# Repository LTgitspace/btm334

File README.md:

# BTM334 Audio Receiver (Archived)

## Project Status: Deprecated & Unmaintained

This repository is **no longer actively maintained or developed**. 

The hardware and firmware designs preserved here represent legacy prototype iterations based on the **Qualcomm QCC3034 (BTM334)** module and external I2S DACs (ES9023P / PCM5102A). This repository is retained strictly for historical and architectural reference.

---

## Technical Migration: ESP32 + LDAC + Custom App

Active development has fully pivoted to an **Espressif ESP32-based architecture** delivering high-resolution wireless audio paired with a dedicated control software ecosystem.

### Key Architectural Shifts

1. **Audio Codec: Sony LDAC Integration**
   * Migrated from Qualcomm proprietary codecs (aptX / aptX HD / aptX LL) to **Sony LDAC**.
   * Capable of streaming 24-bit / 96 kHz high-resolution audio at transmission bitrates up to 990 kbps across standard A2DP profiles.

2. **Core Processor: ESP32 Platform**
   * Replaced the Qualcomm QCC3034 module with an ESP32 dual-core microcontroller running open ESP-IDF firmware.
   * Native, low-jitter I2S digital audio output feeding modern high-fidelity DAC stages.
   * Dual-mode Bluetooth support (Bluetooth Classic A2DP audio sink combined with BLE for control telemetry).

3. **Custom Companion Control Application**
   * Developing a dedicated cross-platform companion application (mobile/desktop).
   * Features real-time parametric EQ control, DSP filter tuning, DAC volume control, battery telemetry, and Over-The-Air (OTA) firmware updating over BLE.

### Rationale for the Pivot
* **Toolchain & Developer Autonomy:** Qualcomm ADK 6.4.2 and MDE 2.3 operate within a closed, vendor-locked ecosystem requiring proprietary debug hardware and restrictive NDA licensing. The ESP-IDF framework provides an open-source, reproducible, and verifiable toolchain.
* **DSP & Clocking Architecture:** Qualcomm Kymera DSP stream endpoints introduced significant clock synthesis constraints (such as MCLK configuration barriers for synchronous external DACs). The ESP32 platform enables deterministic clock control and open DSP filter pipelines.
* **Audio Fidelity:** LDAC achieves significantly higher throughput (990 kbps) compared to aptX HD (576 kbps), offering true high-resolution wireless streaming.

---

## Legacy Archive Contents

The files preserved in this repository document the earlier Qualcomm iterations:
* `btm334/`: KiCad schematic, PCB layout, and mechanical symbol/footprint libraries for the BTM334 receiver revisions (v0.1 ES9023P and v0.2 PCM5102A).
* `example1/`: Qualcomm ADK 6.4.2 Kymera Sink application baseline firmware and flash configuration scripts.
* `AGENTS.md`: Original project design requirements and hardware specifications.

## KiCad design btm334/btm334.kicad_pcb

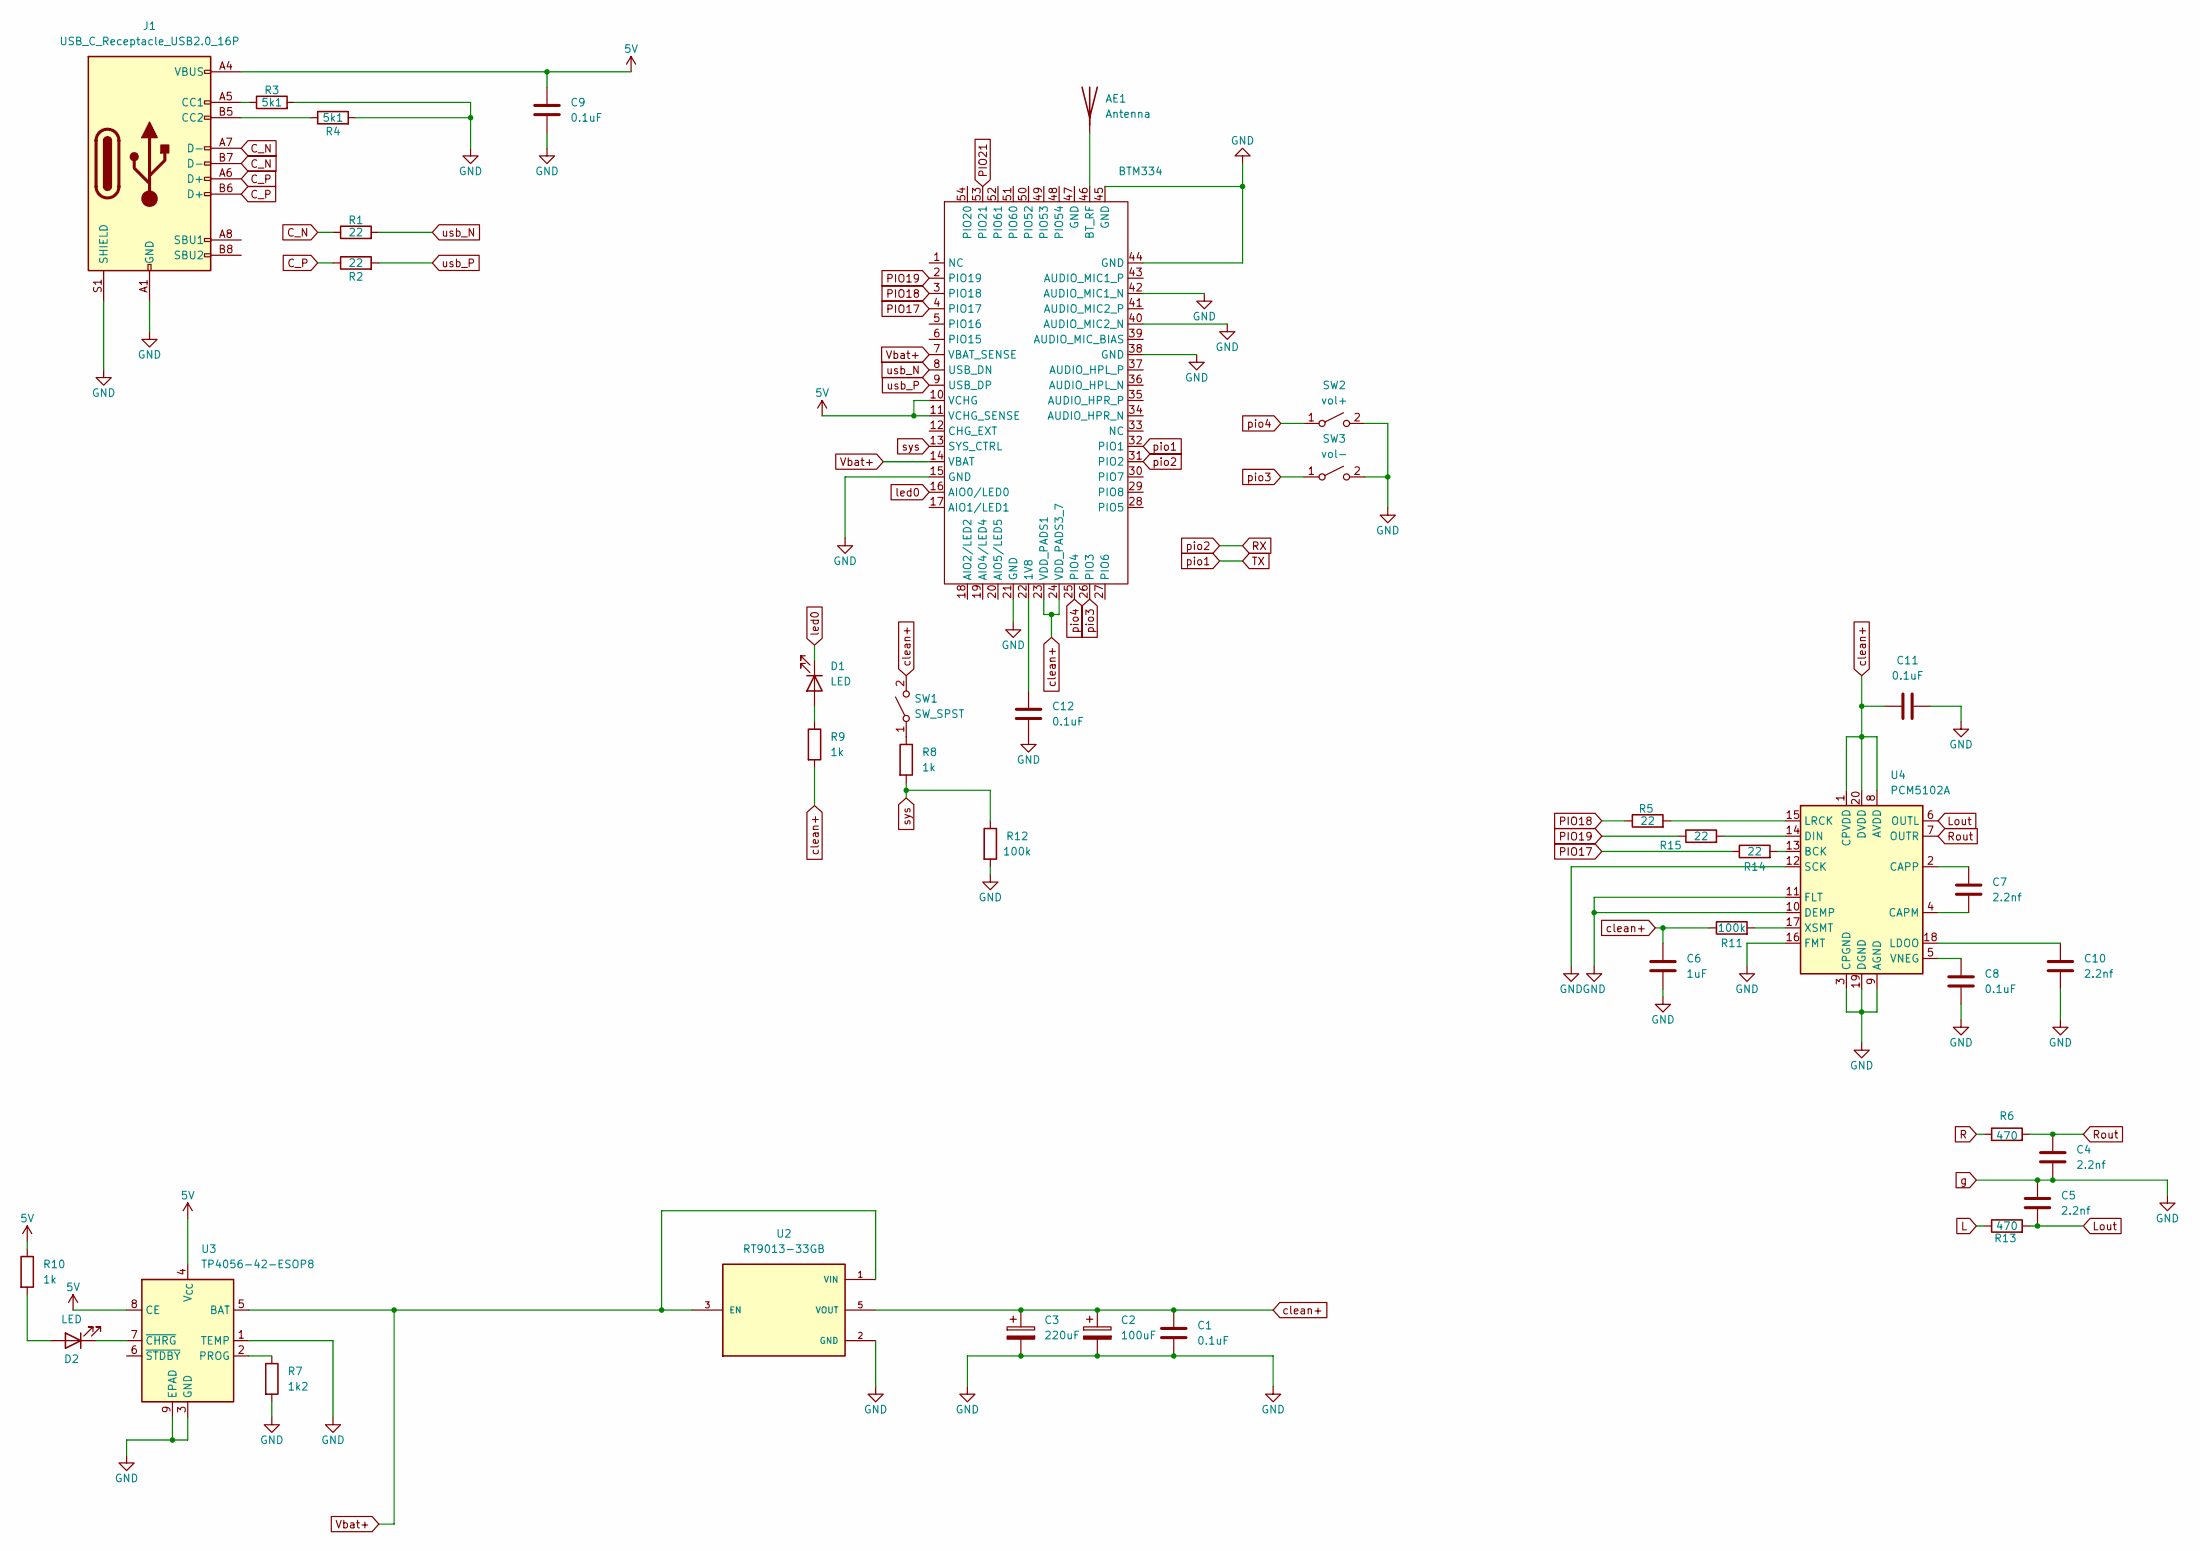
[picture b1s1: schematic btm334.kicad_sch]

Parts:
AE1: Antenna; Texas_SWRA117D_2.4GHz_Left
BTM334: BTM334
C1, C8, C9, C11, C12: 0.1uF; C_0805_2012Metric_Pad1.18x1.45mm_HandSolder
C2: 100uF; CP_Radial_D10.0mm_P5.00mm
C3: 220uF; CP_Radial_D10.0mm_P5.00mm
C4, C5, C7, C10: 2.2nf; C_0805_2012Metric_Pad1.18x1.45mm_HandSolder
C6: 1uF; C_0805_2012Metric_Pad1.18x1.45mm_HandSolder
D1, D2: LED; LED_0805_2012Metric_Pad1.15x1.40mm_HandSolder
J1: USB_C_Receptacle_USB2.0_16P; USB_C_Receptacle_HCTL_HC-TYPE-C-16P-01A
R1, R2: 22; C_0805_2012Metric_Pad1.18x1.45mm_HandSolder
R3, R4: 5k1; C_0805_2012Metric_Pad1.18x1.45mm_HandSolder
R5, R14, R15: 22; R_0805_2012Metric_Pad1.20x1.40mm_HandSolder
R6, R13: 470; L_0805_2012Metric_Pad1.15x1.40mm_HandSolder
R7: 1k2; C_0805_2012Metric_Pad1.18x1.45mm_HandSolder
R8: 1k; L_0805_2012Metric_Pad1.15x1.40mm_HandSolder
R9, R10: 1k; R_0805_2012Metric_Pad1.20x1.40mm_HandSolder
R11: 100k; R_0805_2012Metric_Pad1.20x1.40mm_HandSolder
R12: 100k; L_0805_2012Metric_Pad1.15x1.40mm_HandSolder
SW1: SW_SPST; SW_PUSH_6mm_H13mm
SW2: vol+; SW_PUSH_6mm_H13mm
SW3: vol-; SW_PUSH_6mm_H13mm
U2: RT9013-33GB; TSOT-23-5_HandSoldering; PARTREV Aprill 2011
U3: TP4056-42-ESOP8; SOIC-8-1EP_3.9x4.9mm_P1.27mm_EP2.41x3.3mm_ThermalVias
U4: PCM5102A; TSSOP-20_4.4x6.5mm_P0.65mm

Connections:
5V: BTM334.10 (VCHG), BTM334.11 (VCHG_SENSE), C9.1, J1.A4 (VBUS), J1.A9 (VBUS), J1.B4 (VBUS), J1.B9 (VBUS), R10.1, U3.4 (V_{CC}), U3.8 (CE)
C_N: J1.A7 (D-), J1.B7 (D-), R1.1
C_P: J1.A6 (D+), J1.B6 (D+), R2.1
L: R13.1
Lout: C5.1, R13.2, U4.6 (OUTL)
unnamed: AE1.1 (A), BTM334.46 (BT_RF)
unnamed: BTM334.22 (1V8), C12.2
unnamed: D1.2 (A), R9.1
unnamed: D2.2 (A), R10.2
unnamed: D2.1 (K), U3.7 (~CHRG)
unnamed: J1.A5 (CC1), R3.1
unnamed: J1.B5 (CC2), R4.1
unnamed: R8.1, SW1.1 (A)
unnamed: R7.1, U3.2 (PROG)
unnamed: R14.2, U4.13 (BCK)
unnamed: C7.1, U4.4 (CAPM)
unnamed: C7.2, U4.2 (CAPP)
unnamed: R15.2, U4.14 (DIN)
unnamed: C10.2, U4.18 (LDOO)
unnamed: R5.2, U4.15 (LRCK)
unnamed: C8.2, U4.5 (VNEG)
unnamed: R11.2, U4.17 (XSMT)
PIO17: BTM334.4 (PIO17), R14.1
PIO18: BTM334.3 (PIO18), R5.1
PIO19: BTM334.2 (PIO19), R15.1
PIO21: BTM334.53 (PIO21)
R: R6.1
RX: BTM334.31 (PIO2)
Rout: C4.2, R6.2, U4.7 (OUTR)
TX: BTM334.32 (PIO1)
Vbat+: BTM334.7 (VBAT_SENSE), BTM334.14 (VBAT), U2.1 (VIN), U2.3 (EN), U3.5 (BAT)
clean+: BTM334.23 (VDD_PADS1), BTM334.24 (VDD_PADS3_7), C1.2, C2.1, C3.1, C6.2, C11.2, R9.2, R11.1, SW1.2 (B), U2.5 (VOUT), U4.1 (CPVDD), U4.8 (AVDD), U4.20 (DVDD)
g: BTM334.15 (GND), BTM334.21 (GND), BTM334.38 (GND), BTM334.40 (AUDIO_MIC2_N), BTM334.42 (AUDIO_MIC1_N), BTM334.44 (GND), BTM334.45 (GND), C1.1, C2.2, C3.2, C4.1, C5.2, C6.1, C8.1, C9.2, C10.1, C11.1, C12.1, J1.A1 (GND), J1.A12 (GND), J1.B1 (GND), J1.B12 (GND), J1.S1 (SHIELD), R3.2, R4.2, R7.2, R12.2, SW2.2 (B), SW3.2 (B), U2.2 (GND), U3.1 (TEMP), U3.3 (GND), U3.9 (EPAD), U4.3 (CPGND), U4.9 (AGND), U4.10 (DEMP), U4.11 (FLT), U4.12 (SCK), U4.16 (FMT), U4.19 (DGND)
led0: BTM334.16 (AIO0/LED0), D1.1 (K)
pio3: BTM334.26 (PIO3), SW3.1 (A)
pio4: BTM334.25 (PIO4), SW2.1 (A)
sys: BTM334.13 (SYS_CTRL), R8.2, R12.1
usb_N: BTM334.8 (USB_DN), R1.2
usb_P: BTM334.9 (USB_DP), R2.2

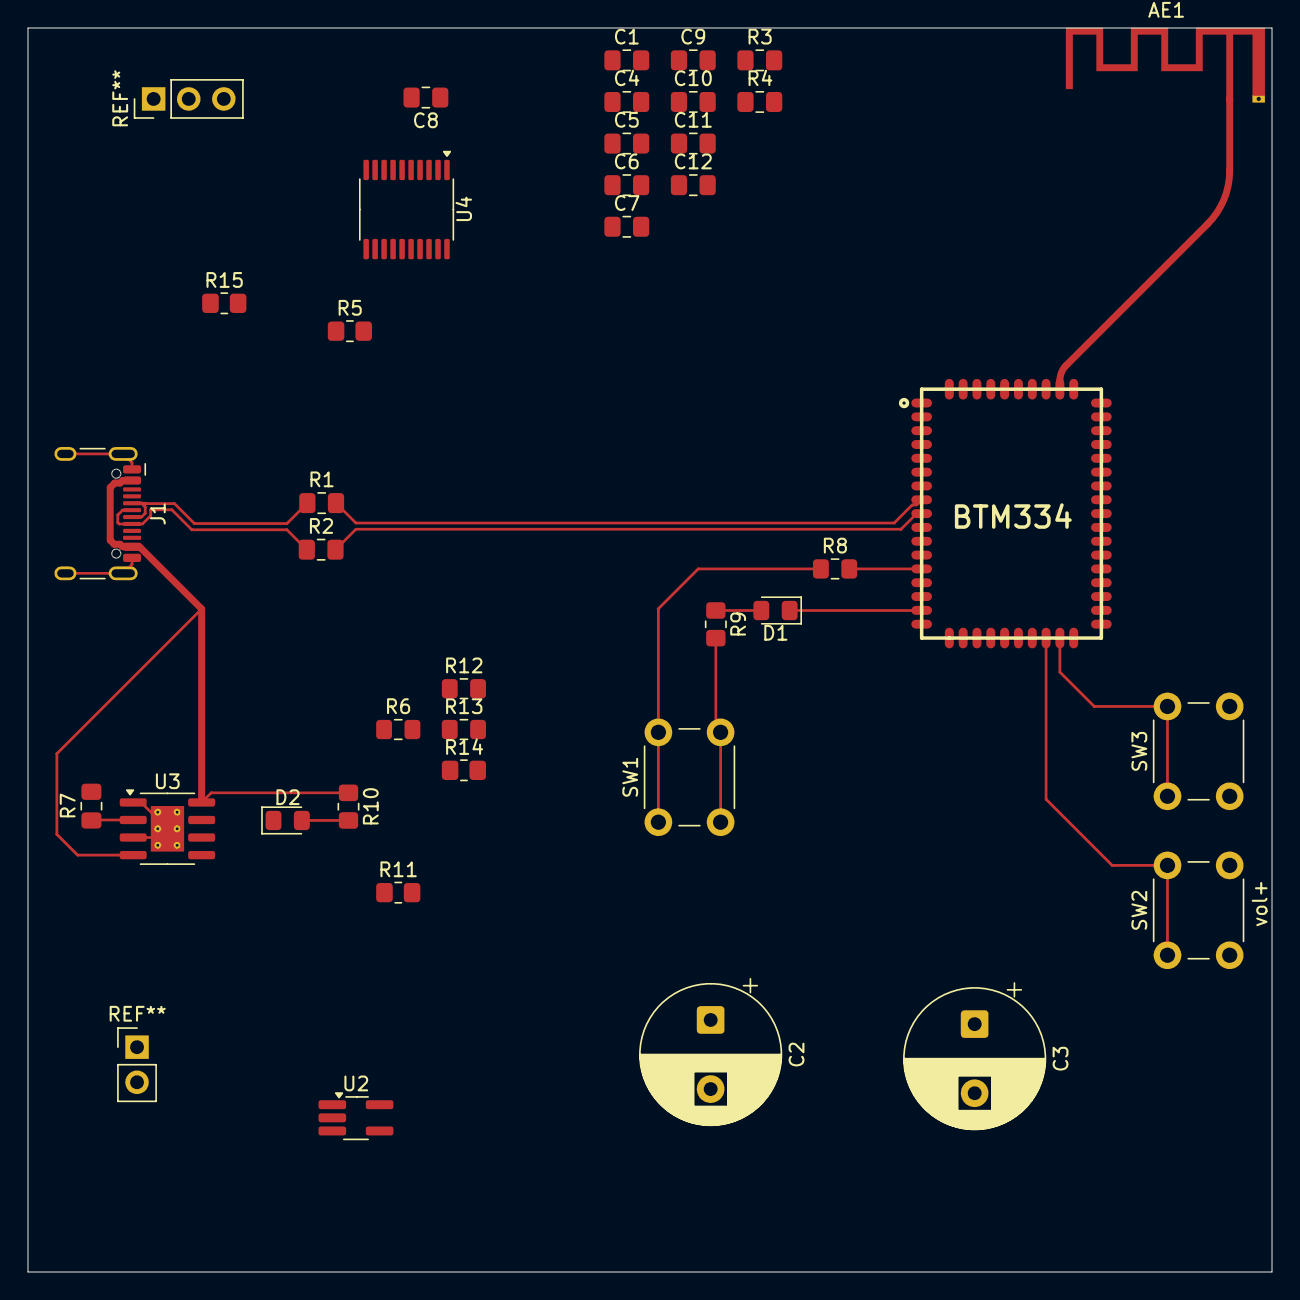
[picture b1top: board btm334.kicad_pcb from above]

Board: 2 copper layers, 90.0 x 90.0 mm, 38 parts (0 on the bottom side), 34 nets.
